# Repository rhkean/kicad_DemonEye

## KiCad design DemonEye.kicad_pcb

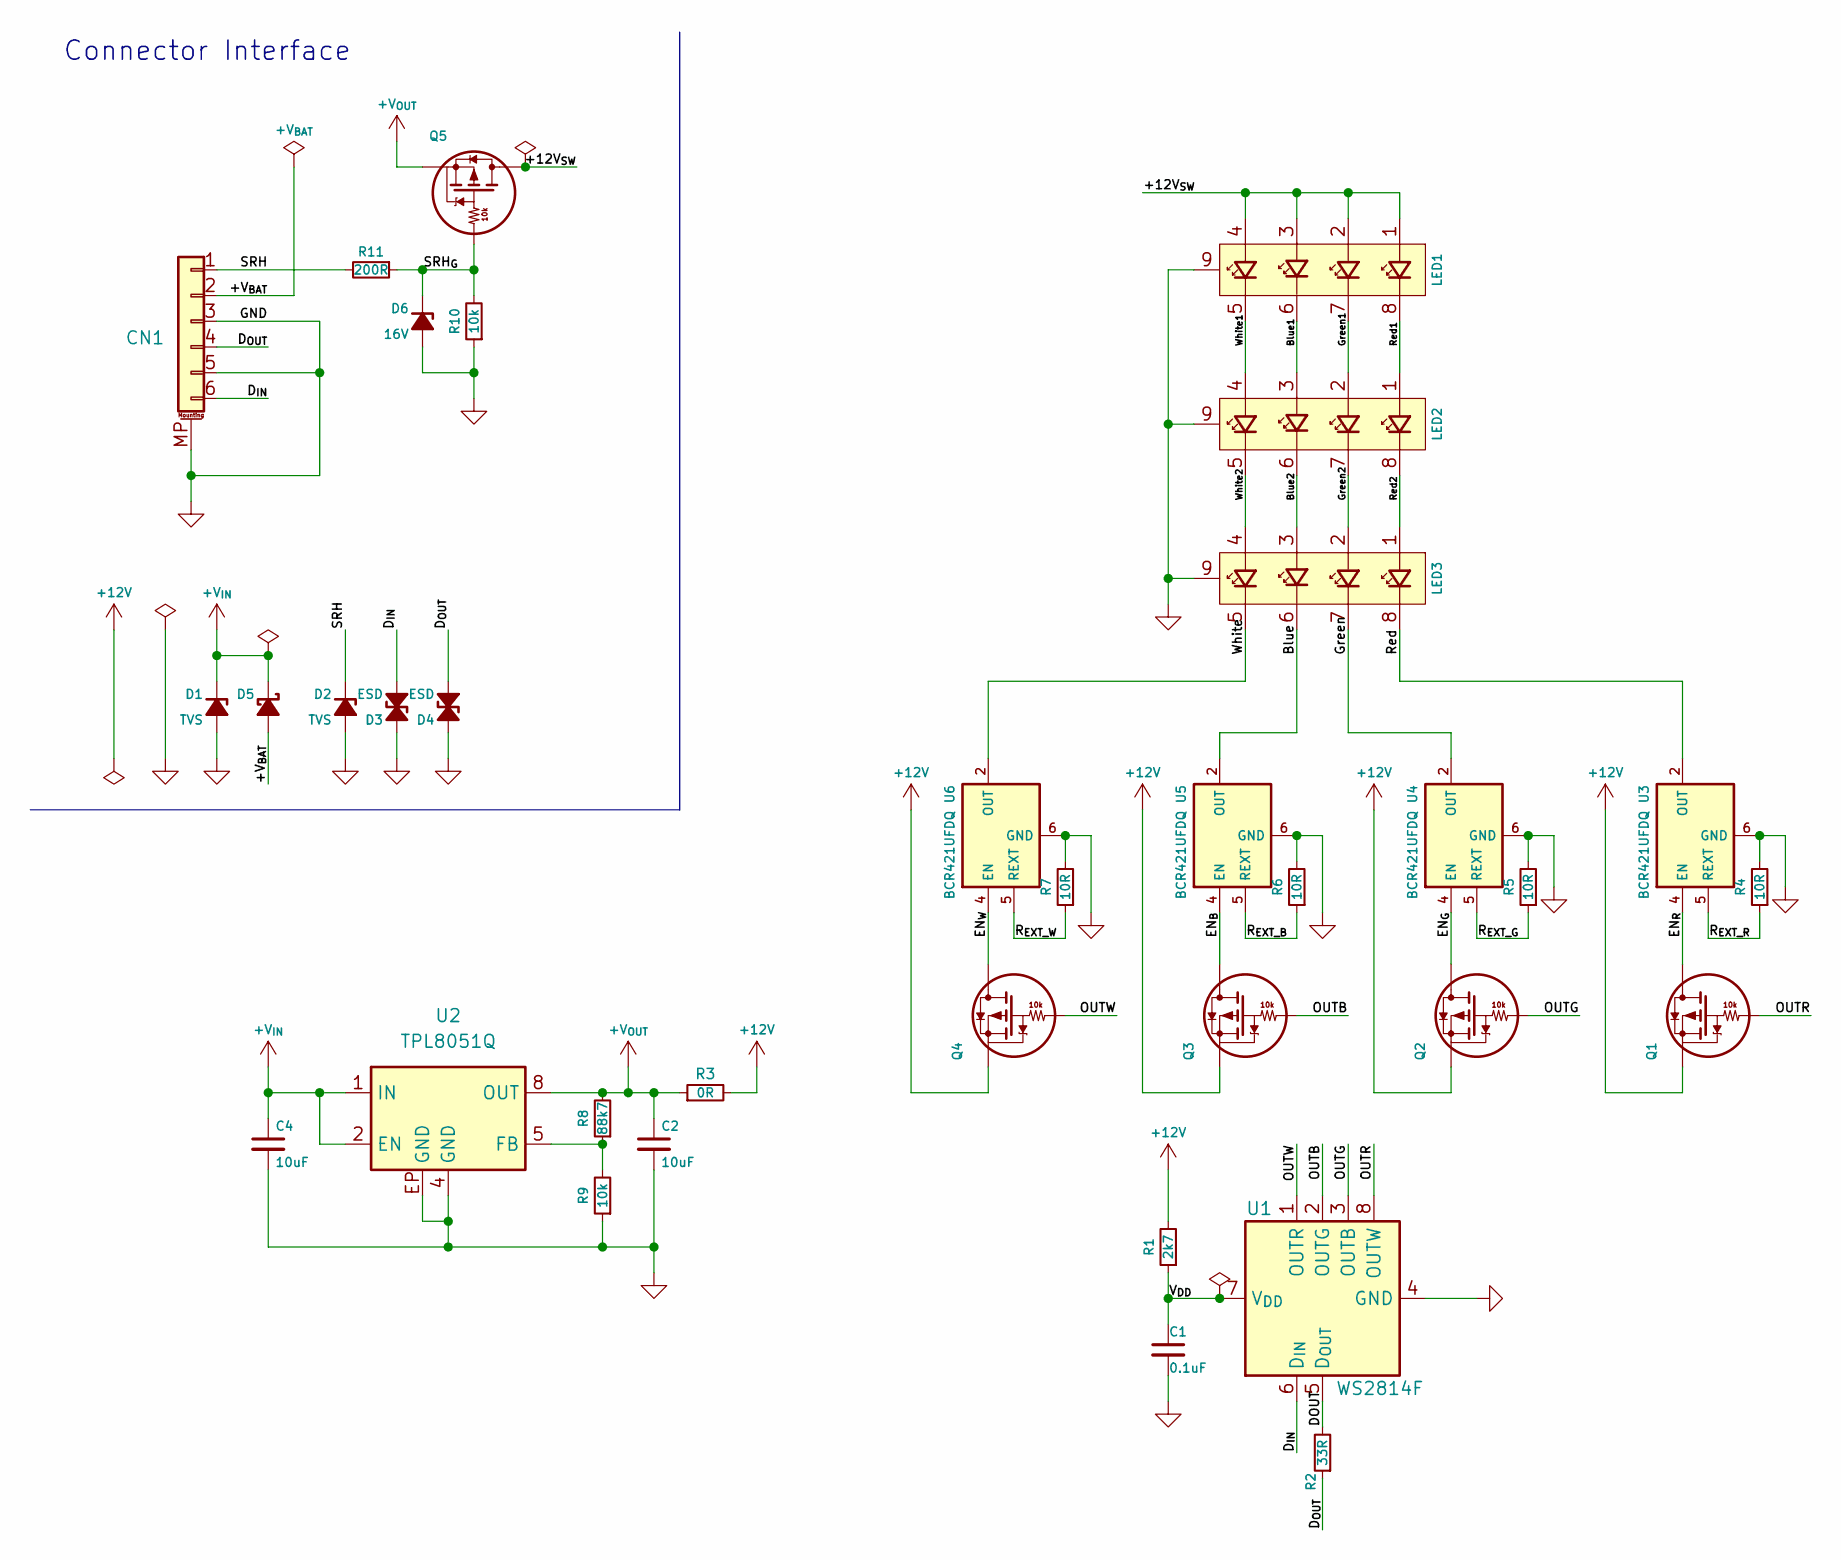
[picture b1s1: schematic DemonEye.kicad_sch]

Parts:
C1: 0.1uF; C_0201_Nominal; Manufacturer Part Number GRT033R61E104KE01D; LCSC C915760
C2, C4: 10uF; C_0805_Nominal; Manufacturer Part Number GCM21BC71E106KE36L; LCSC C5367383
CN1: PicoBlade 1x06 P1.25mm; Molex_PicoBlade_53261-0671_1x06_P1.25mm_Horizontal_SMD; Manufacturer Part Number HC-1.25-6PWT; LCSC C2845383
D1, D2: TVS; DFN1006-2; Manufacturer Part Number D15V0H1U2LP-7B; LCSC C1973850
D3, D4: ESD; DFN1006-2; Manufacturer Part Number SZESD7241N2T5G; LCSC C604770
D5: D_Schottky_Small_Filled; DFN1006-2; MPN NSVR05F40NXT5G; LCSC C604383
D6: 16V; DFN1006-2; Manufacturer Part Number BZX884-C16,315; LCSC C551222
LED1, LED2, LED3: QLSP06RGBXWAJ; Manufacturer Part Number QLSP06RGBXWAJ; LCSC C17645191
Q1, Q2, Q3, Q4, Q5: CSD25501F3; Texas_PICOSTAR-YJN_0.7x0.6mm_PicoStar; Manufacturer Part Number CSD25501F3; LCSC C2872196
R1: 2k7; R_0201_Dense; Manufacturer Part Number AC0201FR-072K7L; LCSC C226497
R2: 33R; R_0402_Nominal; Manufacturer Part Number AC0402FR-0733RL; LCSC C227000
R3: 0R; R_0603_Nominal; Manufacturer Part Number AC0603FR-070RL; LCSC C116699
R4, R5, R6, R7: 10R; R_0201_Dense; MPN AF0201FR-0710RL; LCSC C143979
R8: 88k7; R_0201_Dense; Manufacturer Part Number 0201WMF8872TEE; LCSC C423412
R9: 10k; R_0201_Dense; Manufacturer Part Number AC0201FR-0710KL; LCSC C144833
R10: 10k; R_0201_Nominal; Manufacturer Part Number AC0201FR-0710KL; LCSC C144833
R11: 200R; R_0402_Nominal; Manufacturer Part Number RC0402FR-07200RL; LCSC C114764
U1: WS2814F; FSOP-8_3.25x1.65mm_P0.8mm; Manufacturer Part Number WS2814F; LCSC C5446694
U2: TPL8051Q; DFN-8-1EP_3x3mm_P0.65mm_EP1.55x2.4mm; MPN TPL8051ADQ-DFCR-S; LCSC C48618279
U3, U4, U5, U6: BCR421UFDQ; Manufacturer Part Number BCR421UFDQ-7; LCSC C2678624

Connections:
+12V: Q1.2 (S), Q2.2 (S), Q3.2 (S), Q4.2 (S), R1.2, R3.2
+V_{IN}: C4.1, D1.1 (K), D5.1 (K), U2.1 (IN), U2.2 (EN)
+V_{OUT}: C2.1, Q5.2 (S), R3.1, R8.2, U2.8 (OUT)
/+12V_{SW}: LED1.1 (Red_A), LED1.2 (Green_A), LED1.3 (Blue_A), LED1.4 (White_A), Q5.3 (D)
/+V_{BAT}: CN1.2, D5.2 (A)
/Blue: LED3.6 (Blue_K), U5.2 (OUT)
/Blue1: LED1.6 (Blue_K), LED2.3 (Blue_A)
/Blue2: LED2.6 (Blue_K), LED3.3 (Blue_A)
/DOUT: R2.2, U1.5 (D_{OUT})
/D_{IN}: CN1.6 (Pin_4), D3.1 (A1), U1.6 (D_{IN})
/D_{OUT}: CN1.4, D4.1 (A1), R2.1
/EN_{B}: Q3.3 (D), U5.4 (EN)
/EN_{G}: Q2.3 (D), U4.4 (EN)
/EN_{R}: Q1.3 (D), U3.4 (EN)
/EN_{W}: Q4.3 (D), U6.4 (EN)
/Green: LED3.7 (Green_K), U4.2 (OUT)
/Green1: LED1.7 (Green_K), LED2.2 (Green_A)
/Green2: LED2.7 (Green_K), LED3.2 (Green_A)
/OUTB: Q3.1 (G), U1.2 (OUTG)
/OUTG: Q2.1 (G), U1.3 (OUTB)
/OUTR: Q1.1 (G), U1.8 (OUTW)
/OUTW: Q4.1 (G), U1.1 (OUTR)
/R_{EXT_B}: R6.1, U5.5 (REXT)
/R_{EXT_G}: R5.1, U4.5 (REXT)
/R_{EXT_R}: R4.1, U3.5 (REXT)
/R_{EXT_W}: R7.1, U6.5 (REXT)
/Red: LED3.8 (Red_K), U3.2 (OUT)
/Red1: LED1.8 (Red_K), LED2.1 (Red_A)
/Red2: LED2.8 (Red_K), LED3.1 (Red_A)
/SRH: CN1.1, D2.1 (K), R11.2
/SRH_{G}: D6.1 (K), Q5.1 (G), R10.2, R11.1
/V_{DD}: C1.1, R1.1, U1.7 (V_{DD})
/White: LED3.5 (White_K), U6.2 (OUT)
/White1: LED1.5 (White_K), LED2.4 (White_A)
/White2: LED2.5 (White_K), LED3.4 (White_A)
GND: C1.2, C2.2, C4.2, CN1.3, CN1.5 (Pin_4), CN1.MP (MountPin), D1.2 (A), D2.2 (A), D3.2 (A2), D4.2 (A2), D6.2 (A), LED1.9 (EP), LED2.9 (EP), LED3.9 (EP), R4.2, R5.2, R6.2, R7.2, R9.1, R10.1, U1.4 (GND), U2.4 (GND), U2.EP (GND), U3.6 (GND), U4.6 (GND), U5.6 (GND), U6.6 (GND)
unnamed: R8.1, R9.2, U2.5 (FB)

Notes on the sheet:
Connector Interface

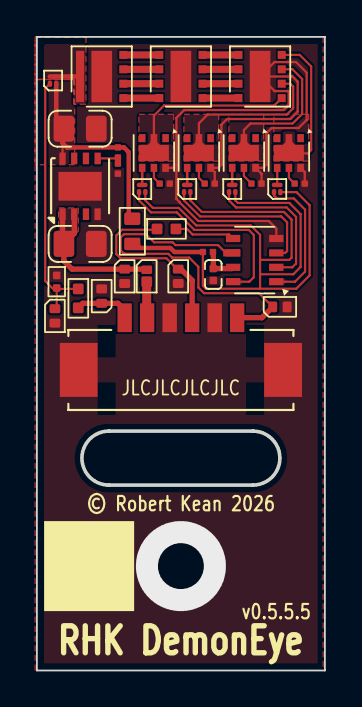
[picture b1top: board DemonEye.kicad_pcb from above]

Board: 2 copper layers, 15.9 x 35.1 mm, 35 parts (0 on the bottom side), 37 nets.

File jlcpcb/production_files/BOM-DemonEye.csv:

Comment,Designator,Footprint,LCSC,Quantity
0.1uF,C1,C_0201_Nominal,C915760,1
0R,R3,R_0603_Nominal,C116699,1
10R,"R4,R5,R6,R7",R_0201_Dense,C143979,4
10k,"R10,R9",R_0201_Nominal,C144833,2
10uF,"C2,C4",C_0805_Nominal,C5367383,2
16V,D6,DFN1006-2,C551222,1
200R,R11,R_0402_Nominal,C114764,1
2k7,R1,R_0201_Dense,C226497,1
33R,R2,R_0402_Nominal,C227000,1
88k7,R8,R_0201_Dense,C423412,1
BCR421UFDQ,"U3,U4,U5,U6",BCR421UFDQ,C2678624,4
CSD25501F3,"Q1,Q2,Q3,Q4,Q5",Texas_PICOSTAR-YJN_0.7x0.6mm_PicoStar,C2872196,5
D_Schottky_Small_Filled,D5,DFN1006-2,C604383,1
ESD,"D3,D4",DFN1006-2,C604770,2
PicoBlade 1x06 P1.25mm,CN1,Molex_PicoBlade_53261-0671_1x06_P1.25mm_Horizontal_SMD,C2845383,1
QLSP06RGBXWAJ,"LED1,LED2,LED3",QLSP06RGBXWAJ,C17645191,3
TPL8051Q,U2,DFN-8-1EP_3x3mm_P0.65mm_EP1.55x2.4mm,C48618279,1
TVS,"D1,D2",DFN1006-2,C1973850,2
WS2814F,U1,FSOP-8_3.25x1.65mm_P0.8mm,C5446694,1

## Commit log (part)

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2026-05-24 Update .gitignore, DemonEye.kicad_pcb, DemonEye.kicad_prl, and 3 more files
2026-05-30 v0.4.0.0
2026-06-04 Update ConstantCurrentWithThermalFoldbackDesign.txt, DemonEye.kicad_pcb, DemonEye.kicad_prl, and 3 more files
2026-06-04 Update DemonEye.kicad_pcb, corrected FemtoFET footprint
2026-06-05 improved spacing on components between pad and silkscreen. required some shifting of components on board
2026-06-05 forgot to hit save
2026-06-05 final revision/sync after messing up other repo and cleaning up silkscreen and pad overlap. Added EP pad for the BJT
2026-06-14 JLCPCB 2026-06-03 11:50:17 PCB: Y60-5297522A PCBA: SMT026060362708-5297522A
2026-06-23 Update DemonEye.kicad_pcb, DemonEye.kicad_prl, DemonEye.kicad_pro, and 8 more files

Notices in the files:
DemonEye.kicad_pcb:
© Robert Kean 2026
